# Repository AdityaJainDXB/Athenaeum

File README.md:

# Athenaeum

Open-source e-ink reader that downloads free books from Archive.org over Wi-Fi, takes notes on what you read, and even serves as a tiny offline viewer for NASA's public data. All on a single custom circuit board.

---

The idea

Since public domain books are free, you can also access The Internet Archive and Open Library with millions of these. NASA has tons of open data too – images from missions, the Astronomy Picture of the Day archive, the Artemis mission logs. But to be used, you need an internet connection, which isn't always available – weak school WiFi, no data plan, off the grid.

The Athenaeum, then, is a little battery powered piece of kit that solves this problem: when you're online, just sync up Athenaeum and it will take all of your books, your notes and a smattering of NASA's free open data with you as far as you go. And it's a multiple app device, too: it's designed as a little plug-in gadget and is capable of running multiple applications.

All of this – schematic, pcb and firmware – was really designed from scratch and is open source.

# It's basically a little computer with an e-ink display

The book reader is the first feature you get, not the only one it has. If you strip it away you end up with an ESP32-S3, a large e-ink display, Wi-Fi, an SD card, and buttons. The firmware is an app launcher, so creating a new feature (a flash card reader, a weather log, whatever) is a change to the firmware, not the design of the board. If you copy this board to create another project, you've already done the electronics.

What it does right now

1. Searches and downloads books from Archive.org / Open Library via Wi-Fi

- Reads them offline on the e-ink display (done) - exists a local library on microSD Would you like to comment? Post your comment or leave your feedback below: Name (required): Email (will not be published) (required): Comments: Submit" /> Submit DisableI want this answerAnswered.
- Allows you to save/flag notes associated with a book and page
- Features a "Space" app that takes NASA's Astronomy Picture of the Day for offline use
- Utilizes a rechargeable battery, charged via USB-C

Actually still on the to-do list that don't require phantom and name scanning: full EPUB rendering (currently just outputs plain text, which is what Archive.org's OCR files are, so this one is already working end to end for many books), APOD image in lieu of just the photo's caption, and a real scrollable book list rather than just "pop" the first file. All in firmware/README.md, as always.

The hardware

- ESP32-S3-WROOM-1 – Wi-Fi, USB native, everything runs on it
- Waveshare 7.5" e-Paper panel (800480), with a Waveshare Driver HAT plus a simple 8-pin header - we couldn't use the raw e-ink panels because they use an undocumented FPC connector, which makes designing a board around non-viable; this was the sane middle ground: still a fully custom PCB, just not re-inventing the display driver electronics as well
- MCP73831: Solves the USB power delivery problem by charging a single cell LiPo from a USB-C power source
- TLV70233 regulator - low standby current because this thing is going to need to sit in somebody's bag for weeks between charges
- microSD for the actual book/note storage
- 7 buttons: 5 for navigation, plus reset, and boot

Enclosure? None (this is designed to be used a bare board, with all the exposed components). The board outline is rounded off to prevent sharp edges, but there is no case concealing it.

Complete schematic & board files are located in /hardware.

# Pin map

| Signal | GPIO | | Signal | GPIO |

|---|---|---|---|---|

| EPD_CS | 10 | | Button: Up | 4 |

" /> Button: Up Button: Down | EPD_DC | 11 | | Button: Up | 5 |

| EPD_RST | 12 | | Button: Choose | 6 |

| EPD_BUSY | 13 | | Button: back | 7 |

Button: Menu 8 EPD_SCK 14

| EPD_MOSI | 15 | | SD CS | 16 |

| | | | SD MISO | 17 |

(SPI clock and MOSI are the same for display and SD card - separate CS lines are used for each, that is the correct design, not a shortcut.)

Repo layout

``

athenaeum/

hardware/

kicad/ KiCad project - schematic + PCB

gerbers/ Manufacturing files for JLCPCB

BOM.csv All parts list, with LCSC part numbers

firmware/ ESP32-S3 firmware (PlatformIO)

docs/ Build guide

`

Building one yourself

1. Upload the following data to the JLCPCB PCB Assembling: hardware/gerbers/ and hardware/BOM.csv
2. Flash the firmware - see firmware/README.md.
3. Insert the Waveshare Driver HAT + panel into the 8-pin header (J2).

Full walkthrough: docs/BUILDGUIDE.md.

Where things stand

- [x] Schematic - designed and verified
- [x] PCB - routed, DRC clean
- [x] Gerbers/BOM exported, ready for JLCPCB
- [x] Firmware - app launcher, Wi-Fi + Archive.org search/download, plain-text reading,
Scrollable book browser real on-device note-taking Space app
- [ ] EPUB parsing (accepts only plaintext atm)
- [ ] APOD image rendering (This is just text now)

- [ ] Demo video

Firmware limitations, stated plainly

This is a real, working firmware skeleton, not a finished article - worth being upfront

About exactly what it does and doesn't do so far:

- No EPUB support as yet. It only supports plain .txt files. Which just happens to be quite a lot of files.
Read already, as Archive.org's OCR'd texts come as .txt search
Download browse read works end to end for many public-domain books. EPUB actual The end Works The Bookshelf So when I teach my readers will lead to the works I read, in their works just to pass a great conversation, or even for passes… because I read in them.
(unzipping the container, parsing XHTML/CSS on-device) is an additional, substantial chunk.
 Of work, not yet started.
- All NASA APOD is text-only. It retrieves and displays the current day's title and date as well as the day's.
Explanation – but it is not the real photo. Rendering a true image on e-ink is
Download, JPEG-decoding, scaling, and dithering the image to 1-bit - has not even started.
- Character by character (single entry) picker, because there's no keyboard - it
Works, but writing anything that is of any length is slow. So a reasonably fast input scheme is the next step in design
 step.
- It hasn't been assembled and run on real hardware. It was written with great care against
The right libraries and the actual pcb pinout and there was a build missing too(ESP32).
Environment that I could use to test it during the development of this repo. Expect a standard
First-build debugging pass (a library version mismatch, an exact display-panel class
(name to confirm)and not a guaranteed 'perfect' first flash.

Full detail in firmware/README.md`.

License

Hardware (schematic, PCB): CERN-OHL-S v2. Firmware: MIT.

Thanks to

Open source projects Inkplate, Flick Book for previous E-ink reader, Waveshare for their Driver HAT docs, and Archive.org / Open Library for maintaining an open API.

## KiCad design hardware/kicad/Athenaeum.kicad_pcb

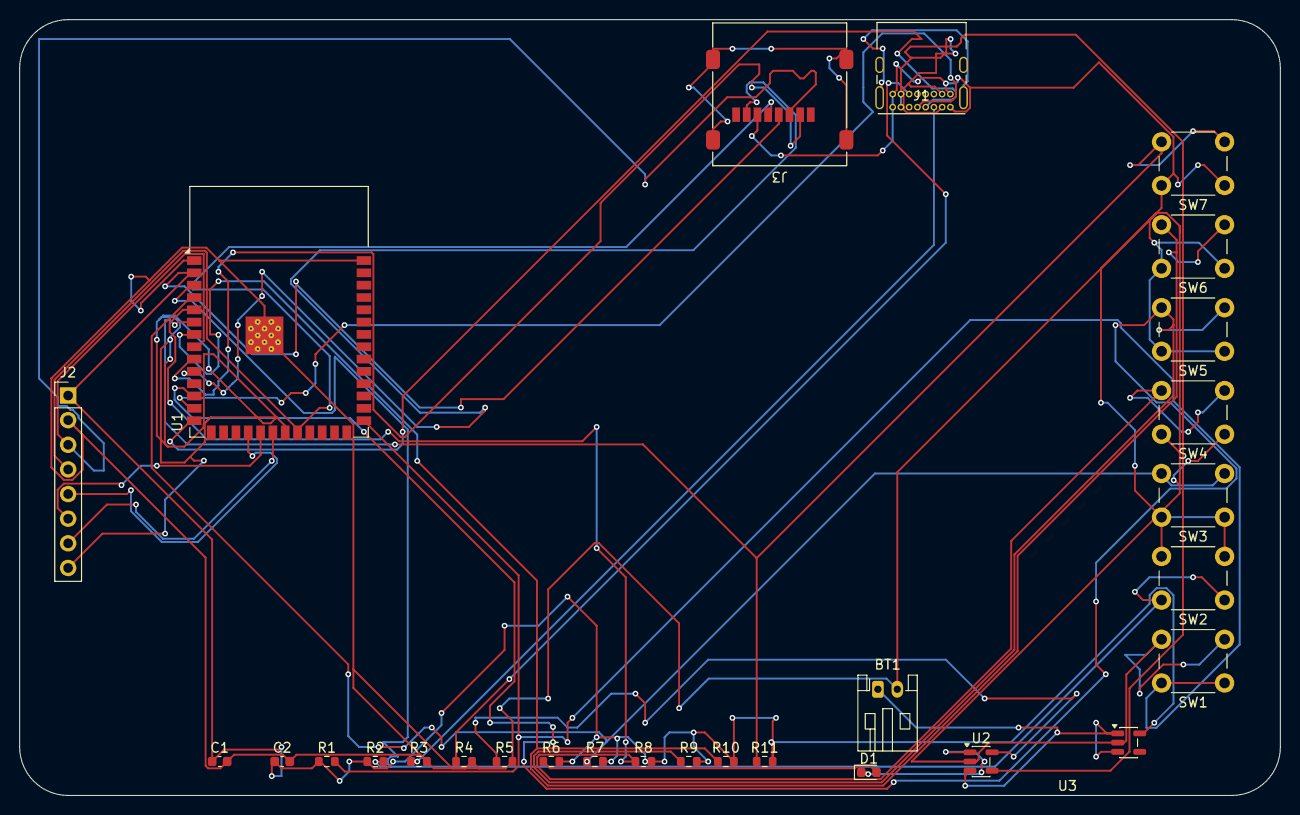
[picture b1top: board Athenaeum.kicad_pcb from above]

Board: 2 copper layers, 130.0 x 80.0 mm, 28 parts (0 on the bottom side), 26 nets.

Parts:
BT1: Battery_Cell; JST_PH_S2B-PH-K_1x02_P2.00mm_Horizontal
C1: 100nF; C_0603_1608Metric
C2: 10uF; C_0603_1608Metric
D1: LED; LED_0603_1608Metric
J1: USB_C_Receptacle_USB2.0_14P; USB_C_Receptacle_GCT_USB4085
J2: Conn_01x08; PinHeader_1x08_P2.54mm_Vertical
J3: Micro_SD_Card_Det1; microSD_HC_Molex_47219-2001
R1, R2, R7, R8, R9, R10, R11: 10k; R_0603_1608Metric
R3, R4: 5.1k; R_0603_1608Metric
R5: 2k; R_0603_1608Metric
R6: 1k; R_0603_1608Metric
SW1, SW2, SW3, SW4, SW5, SW6, SW7: SW_Push; SW_PUSH_6mm
U1: ESP32-S3-WROOM-1
U2: MCP73831-2-OT; SOT-23-5
U3: TLV70233_SOT23-5; SOT-23-5

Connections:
/3V3: C1.1, C2.1, J2.1, J3.4 (VDD), R1.1, R2.1, R6.2, R7.2, R8.2, R9.2, R10.2, R11.2, U1.2 (3V3), U3.5 (OUT)
/EDP_BUSY: J2.8, U1.21 (IO13)
/EDP_CS: J2.5, U1.18 (IO10)
/EDP_DC: J2.6, U1.19 (IO11)
/EDP_MOSI: J2.3, J3.3 (CMD), U1.8 (IO15)
/EDP_RST: J2.7, U1.20 (IO12)
/EDP_SCK: J2.4, J3.5 (CLK), U1.22 (IO14)
GND: BT1.2 (-), C1.2, C2.2, J1.A1 (GND), J1.A12 (GND), J1.B1 (GND), J1.B12 (GND), J2.2, J3.6 (VSS), R3.2, R4.2, R5.2, SW1.2, SW2.2, SW3.1, SW4.1, SW5.1, SW6.1, SW7.1, U1.1 (GND), U1.40 (GND), U1.41 (GND), U2.2 (V_{SS}), U3.2 (GND)
unnamed: BT1.1 (+), U2.3 (V_{BAT}), U3.1 (IN), U3.3 (EN)
unnamed: D1.2 (A), R6.1
unnamed: D1.1 (K), U2.1 (STAT)
unnamed: J1.A5 (CC1), R3.1
unnamed: J1.B5 (CC2), R4.1
unnamed: J3.7 (DAT0), U1.10 (IO17)
unnamed: J3.2 (DAT3/CD), U1.9 (IO16)
unnamed: R2.2, SW2.1, U1.3 (EN)
unnamed: R1.2, SW1.1, U1.27 (IO0)
unnamed: R7.1, SW3.2, U1.4 (IO4)
unnamed: R8.1, SW4.2, U1.5 (IO5)
unnamed: R11.1, SW7.2, U1.6 (IO6)
unnamed: R10.1, SW6.2, U1.7 (IO7)
unnamed: R9.1, SW5.2, U1.12 (IO8)
unnamed: J1.A6 (D+), U1.14 (USB_D+)
unnamed: J1.A7 (D-), U1.13 (USB_D-)
unnamed: R5.1, U2.5 (PROG)
unnamed: J1.A4 (VBUS), J1.A9 (VBUS), J1.B4 (VBUS), J1.B9 (VBUS), U2.4 (V_{DD})

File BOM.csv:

Designator,Value,Footprint,LCSC Part,Description,Approx Unit Cost (USD),Qty
U1,ESP32-S3-WROOM-1,RF_Module:ESP32-S3-WROOM-1,C2913198,ESP32-S3 Wi-Fi/BLE module 8MB flash,~2.50,1
U2,MCP73831-2-OT,Package_TO_SOT_SMD:SOT-23-5,C424093,LiPo linear charge management IC (4.2V),~0.15,1
U3,TLV70233_SOT23-5,Package_TO_SOT_SMD:SOT-23-5,C110287,3.3V low-IQ LDO regulator,~0.20,1
J1,USB_C_Receptacle_USB2.0_14P,Connector_USB:USB_C_Receptacle_GCT_USB4085,,USB-C receptacle (power + data),~0.30,1
J2,Conn_01x08,Connector_PinHeader_2.54mm:PinHeader_1x08_P2.54mm_Vertical,,8-pin header to e-Paper Driver HAT,~0.10,1
J3,Micro_SD_Card_Det1,Connector_Card:microSD_HC_Molex_47219-2001,,microSD card socket,~0.40,1
BT1,Battery_Cell,Connector_JST:JST_PH_S2B-PH-K_1x02_P2.00mm_Horizontal,,JST-PH 2-pin battery connector,~0.10,1
D1,LED,LED_SMD:LED_0603_1608Metric,,Charging status LED,~0.02,1
C1,100nF,Capacitor_SMD:C_0603_1608Metric,,Decoupling capacitor,~0.01,1
C2,10uF,Capacitor_SMD:C_0603_1608Metric,,Bulk decoupling capacitor,~0.02,1
R1,10k,Resistor_SMD:R_0603_1608Metric,,Boot (GPIO0) pull-up,~0.01,1
R2,10k,Resistor_SMD:R_0603_1608Metric,,Reset (EN) pull-up,~0.01,1
R3,5.1k,Resistor_SMD:R_0603_1608Metric,,USB-C CC1 pull-down,~0.01,1
R4,5.1k,Resistor_SMD:R_0603_1608Metric,,USB-C CC2 pull-down,~0.01,1
R5,2k,Resistor_SMD:R_0603_1608Metric,,Charge current set (PROG),~0.01,1
R6,1k,Resistor_SMD:R_0603_1608Metric,,Status LED current limit,~0.01,1
R7,10k,Resistor_SMD:R_0603_1608Metric,,Button pull-up (Up),~0.01,1
R8,10k,Resistor_SMD:R_0603_1608Metric,,Button pull-up (Down),~0.01,1
R9,10k,Resistor_SMD:R_0603_1608Metric,,Button pull-up (Menu),~0.01,1
R10,10k,Resistor_SMD:R_0603_1608Metric,,Button pull-up (Back),~0.01,1
R11,10k,Resistor_SMD:R_0603_1608Metric,,Button pull-up (Select),~0.01,1
SW1,SW_Push,Button_Switch_THT:SW_PUSH_6mm,,Boot button,~0.05,1
SW2,SW_Push,Button_Switch_THT:SW_PUSH_6mm,,Reset button,~0.05,1
SW3,SW_Push,Button_Switch_THT:SW_PUSH_6mm,,Nav button: Up,~0.05,1
SW4,SW_Push,Button_Switch_THT:SW_PUSH_6mm,,Nav button: Down,~0.05,1
SW5,SW_Push,Button_Switch_THT:SW_PUSH_6mm,,Nav button: Menu,~0.05,1
SW6,SW_Push,Button_Switch_THT:SW_PUSH_6mm,,Nav button: Back,~0.05,1
SW7,SW_Push,Button_Switch_THT:SW_PUSH_6mm,,Nav button: Select,~0.05,1

Off-board items (not part of PCB assembly order):
Item,Description,Approx Cost (USD),Qty
Waveshare 7.5" e-Paper panel (800x480 mono),Main display,~35-45,1
Waveshare Universal e-Paper Driver HAT,FPC-to-header display adapter,~10,1
Single-cell LiPo battery (JST-PH connector),Power source - capacity TBD based on enclosure size,~5-8,1

Note: unit costs are approximate JLCPCB/LCSC catalog estimates as of design time and should be
re-verified at checkout, since component pricing and stock fluctuate. PCB fabrication and assembly
service fees (setup, extended-part fees, shipping) are separate from per-component costs above.
